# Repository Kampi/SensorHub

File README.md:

# SensorHub

## Table of Contents

- [SensorHub](#sensorhub)
  - [Table of Contents](#table-of-contents)
  - [About](#about)
  - [Image sources](#image-sources)
  - [Setup](#setup)
  - [Device modes](#device-modes)
  - [Bluetooth](#bluetooth)
  - [Measurement](#measurement)
  - [History](#history)
  - [Maintainer](#maintainer)

## About

Solar-powered, low energy environment sensor node with WiFi interface. The device will measure the following parameter:

- Temperature (with a [MCP9808](http://ww1.microchip.com/downloads/en/DeviceDoc/25095A.pdf))
- Humidity (with a [BME680](https://www.bosch-sensortec.com/media/boschsensortec/downloads/datasheets/bst-bme680-ds001.pdf))
- Pressure (with a [BME680](https://www.bosch-sensortec.com/media/boschsensortec/downloads/datasheets/bst-bme680-ds001.pdf))
- Gas resistance (with a [BME680](https://www.bosch-sensortec.com/media/boschsensortec/downloads/datasheets/bst-bme680-ds001.pdf))
- Ambient light (with a [BH1726](https://fscdn.rohm.com/en/products/databook/datasheet/ic/sensor/light/bh1726nuc-e.pdf))
- UV (with a [VEML6070](https://www.vishay.com/docs/84277/veml6070.pdf))

The whole device is designed for low power operation and for a solar panel as current source. A backup battery will be used to buffer the sun-free time during the night or on cloudy days.
This battery will be charged by an integrated solar-charging circuit.

The integrated WiFi is used to transmit the data as an [MQTT](http://mqtt.org/) message to a broker (i. e. a Raspberry Pi). The included Qt application for the Raspberry Pi can be used to visualize and record the received data.

Please visit the [project site](https://www.kampis-elektroecke.de/wetterdaten-aufzeichnen/) or write me an [e-mail](mailto:DanielKampert@kampis-elektroecke.de) when you need additional informations or if you have any questions.

## Image sources

- [Language Icons](https://www.iconfinder.com/iconsets/flags_gosquared)
- [Icons8](https://icons8.com/icon/set/database/material)
- [Qt project](https://www.qt.io/blog/2016/06/20/introducing-new-built-with-qt-logo)

## Setup

- You have to use the [Particle CLI](https://docs.particle.io/reference/developer-tools/cli/) or the [Particle App](https://play.google.com/store/apps/details?id=io.particle.android.app&hl=de) to setup your WiFi credentials in the microcontroller module before you can use the software.

```bash
$ particle usb start-listening
Done.

$ particle serial wifi
? Should I scan for nearby Wi-Fi networks? (Y/n) y
? Should I scan for nearby Wi-Fi networks? Yes
? SSID ...
? SSID ...
? Security Type (Use arrow keys)
? Security Type ...
? Cipher Type (Use arrow keys)
? Cipher Type ...
? Wi-Fi Password ...
? Wi-Fi Password ...
Done! Your device should now restart.
```

- Download a bluetooth app for your smartphone (i. e. [nRF Connect](https://play.google.com/store/apps/details?id=no.nordicsemi.android.mcp&hl=de)).
- Make sure that your microcontroller module runs at least firmware version [1.5.2](https://github.com/particle-iot/device-os/releases/tag/v1.5.2).
- **Optional:** Build the firmware from the soures in `software/SensorHub` by using [Visual Studio Code](https://code.visualstudio.com/) and the [Particle Workbench](https://www.particle.io/workbench/).
- Power up the `SensorHub` and flash the firmware from `software/release` by using the [Particle CLI](https://docs.particle.io/tutorials/developer-tools/cli/#flashing-over-serial-for-the-electron).
- Hold the `MODE` button of the microcontroller module to enter the setup mode.
- After entering the setup mode the RGB LED of the device will lights up red.
- Open the app and connect your smartphone with the `SensorHub`. When the connection is successful the RGB LED of the `SensorHub` starts to blink green until. The device is now ready for configuration until you close the connection.

## Device modes

The `SensorHub` use the RGB led of the microcontroller module to display his current state. Each state is encoded in a blink pattern which begins with a **3 seconds** group color.

| **RGB color** | **Group** |
|:-------------:|:---------:|
| Blue          | Sensors   |
| Green         | Network   |
| Red           | Device    |

The group color is followed by the error code which is encoded with a white flashing of the RGB LED. Each flash has a duration of **1 second**.

| **Blink code** | **Sensors** | **Network** | **Device** |
|:--------------:|:------------------------------------------:|:-----------:|:-----------:|
| 1x             | Temperature sensor failure. | No valid WiFi credentials found. <br> Please use the [Particle CLI](https://docs.particle.io/reference/developer-tools/cli/) to setup your WiFi credentials. | - |
| 2x             | Light sensor failure. | No valid IP address found. | - |
| 3x             | Environment sensor failure. | Connection error. | - |
| 4x             | UV sensor failure. | Network timeout. | - |
| 5x             | Communication error. | - | - |

The current device error is also printed over the serial interface of the microcontroller module or is published over the MQTT tag `sensorhub/errors` (this required valid network settings).

## Bluetooth

The firmware use the following UUIDs for the bluetooth low energy service:

| **UUID** | **Description** |
|:------------------------------------:|:---------:|
| b4250401-fb4b-4746-b2b0-93f0e61122c6 | General service UUID for the BLE service. |
| b4250402-fb4b-4746-b2b0-93f0e61122c6 | MQTT broker IP UUID to configure the IP address of the MQTT broker. |
| b4250403-fb4b-4746-b2b0-93f0e61122c6 | MQTT broker port UUID to configure the port of the MQTT broker. |
| b4250404-fb4b-4746-b2b0-93f0e61122c6 | Sleep time UUID to configure the sleep time of the firmware. |

## Measurement

After a successful configuration and initialization the device will enter the sleep mode. The microcontroller is woken up every three minutes to read in new data from the sensors. After a successful read of the
sensors the data gets packed in a [JSON](https://www.json.org/json-en.html) structure and published by using the [MQTT](http://mqtt.org/) protocol. The firmware uses the topics `sensorhub/weather` to publish the sensor data and the topics `sensorhub/system` and `sensorhub/errors` to publish system messages in the network.
The JSON objects uses the following structure:

`sensorhub/weather`:

```json
{
  "Temperature": "23.0",
  "Ambient light": "1000.0",
  "UV": "7",
  "Pressure": "1004",
  "Humidity": "44.0",
  "Gas resistance": "20000",
  "Gas valid": "0",
  "IAQ": "97.5",
  "IAQ valid": "0",
}
```

`sensorhub/system`:

```json
{
  "Solar": "1.2",
  "Battery": "3.3"
}
```

`sensorhub/errors`:

```txt
This is an error message
```

| **Element**    | **Description** |
|:--------------:|:---------------:|
| Temperature    | Temperature as float in °C. |
| Ambient light  | Illuminance as float in lux. |
| UV             | UV-A index as byte in the range of 0 to 11. |
| Pressure       | Air pressure as float in hPa. |
| Humidity       | Humidity as float in %RH. |
| Gas resistance | Gas resistance as float in Ohms. |
| Gas valid      | Boolean flag to indicate a valid gas measurement. |
| IAQ            | [Indor Air Quality](https://en.wikipedia.org/wiki/Indoor_air_quality) in %. |
| IAQ valid      | Boolean flag to indicate a valid IAQ index. |
| Solar          | Solar cell voltage as float in V. |
| Battery        | Battery voltage as float in V. |

## History

| **Version**   | **Description** | **Date**   |
|-------------|---------------------------------------------|----------|
| 0.1           | Release hardware version 1.1 <br> Firmware version 1.0 <br> Release application version 1.0 | 13.07.2020 |
| 0.2           | Release hardware version 1.2 <br> Improve firmware and release firmware 1.1 <br> Release application version 1.1 | 18.07.2020 |
| 0.3           | Release housing version 1.0 <br> Release firmware 1.2|  |

## Maintainer

- [Daniel Kampert](mailto:DanielKampert@kampis-elektroecke.de)

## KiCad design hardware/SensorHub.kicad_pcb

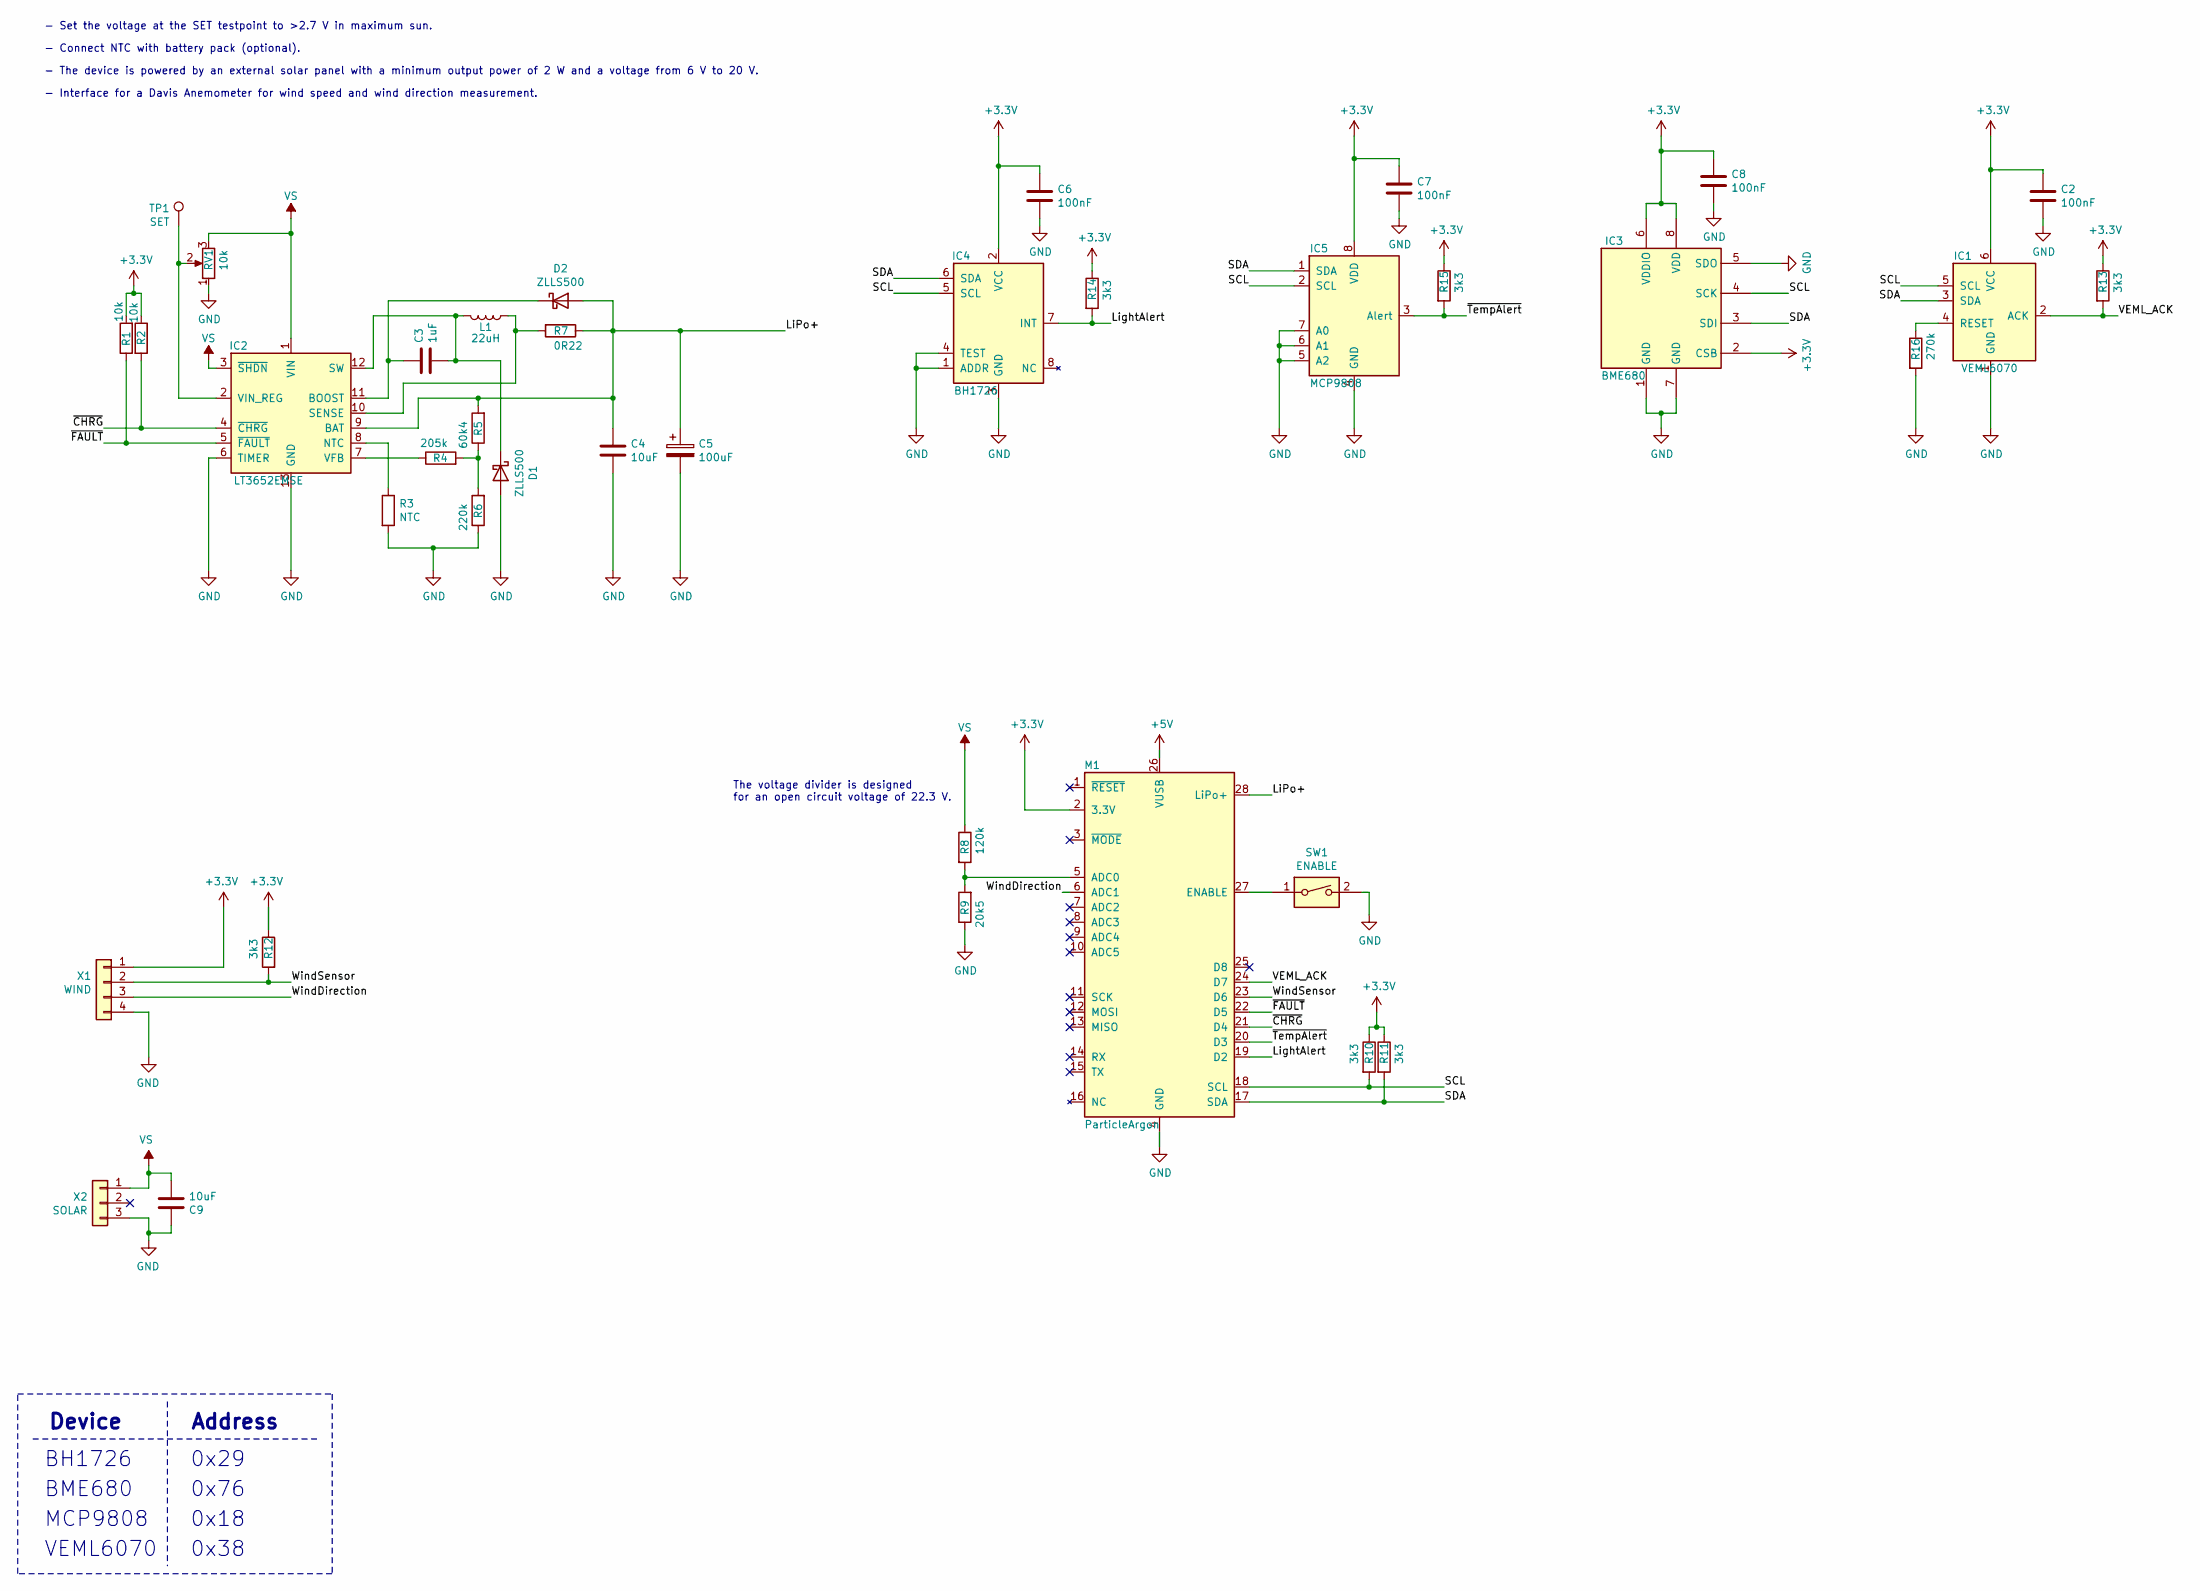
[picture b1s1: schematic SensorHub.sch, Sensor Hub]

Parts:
C2, C6, C7, C8: 100nF; C_0805_2012Metric_Pad1.15x1.40mm_HandSolder
C3: 1uF; C_0805_2012Metric_Pad1.15x1.40mm_HandSolder
C4, C9: 10uF; C_0805_2012Metric_Pad1.15x1.40mm_HandSolder
C5: 100uF; CP_EIA-1608-08_AVX-J_Pad1.25x1.05mm_HandSolder
D1, D2: ZLLS500; D_SOT-23_ANK
IC1: VEML6070; OPLGA-6
IC2: LT3652EMSE; MSOP-12-1EP_3x4mm_P0.65mm_EP1.65x2.85mm
IC3: BME680; Bosch_LGA-8_3x3mm_P0.8mm_ClockwisePinNumbering
IC4: BH1726; WSON-8-1EP_2x2mm_P0.5mm_EP0.9x1.6mm
IC5: MCP9808; MSOP-8_3x3mm_P0.65mm; Mouser 579-MCP9808T-E/MS
L1: 22uH; L_2512_6332Metric_Pad1.52x3.35mm_HandSolder
M1: ParticleArgon; Mfr. Particle
R1, R2: 10k; R_0805_2012Metric_Pad1.15x1.40mm_HandSolder
R3: NTC; PinHeader_1x02_P2.54mm_Vertical
R4: 205k; R_0805_2012Metric_Pad1.15x1.40mm_HandSolder
R5: 60k4; R_0805_2012Metric_Pad1.15x1.40mm_HandSolder
R6: 220k; R_0805_2012Metric_Pad1.15x1.40mm_HandSolder
R7: 0R22; R_0805_2012Metric_Pad1.15x1.40mm_HandSolder
R8: 120k; R_0805_2012Metric_Pad1.15x1.40mm_HandSolder
R9: 20k5; R_0805_2012Metric_Pad1.15x1.40mm_HandSolder
R10, R11, R12, R13, R14, R15: 3k3; R_0805_2012Metric_Pad1.15x1.40mm_HandSolder
R16: 270k; R_0805_2012Metric_Pad1.15x1.40mm_HandSolder
RV1: 10k; Potentiometer_Vishay_TS53YJ_Vertical
SW1: ENABLE; SW_DIP_SPSTx01_Slide_Omron_A6S-110x_W8.9mm_P2.54mm
TP1: SET; TestPoint_Pad_1.5x1.5mm
X1: WIND; 3-2172067-2
X2: SOLAR; 2-2172067-2

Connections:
+3V3: C2.1, C6.1, C7.1, C8.1, IC1.6 (VCC), IC3.2 (CSB), IC3.6 (VDDIO), IC3.8 (VDD), IC4.2 (VCC), IC5.8 (VDD), M1.2 (3.3V), R1.2, R2.1, R10.1, R11.1, R12.1, R13.1, R14.1, R15.1, X1.1
+5V: M1.26 (VUSB)
/LiPo+: C4.1, C5.1, D2.2 (A), IC2.9 (BAT), M1.28 (LiPo+), R5.2, R7.1
/LightAlert: IC4.7 (INT), M1.19 (D2), R14.2
/SCL: IC1.5 (SCL), IC3.4 (SCK), IC4.5 (SCL), IC5.2 (SCL), M1.18 (SCL), R10.2
/SDA: IC1.3 (SDA), IC3.3 (SDI), IC4.6 (SDA), IC5.1 (SDA), M1.17 (SDA), R11.2
/VEML_ACK: IC1.2 (ACK), M1.24 (D7), R13.2
/WindDirection: M1.6 (ADC1), X1.3
/WindSensor: M1.23 (D6), R12.2, X1.2
/~CHRG: IC2.4 (~CHRG), M1.21 (D4), R2.2
/~FAULT: IC2.5 (~FAULT), M1.22 (D5), R1.1
/~TempAlert: IC5.3 (Alert), M1.20 (D3), R15.2
GND: C2.2, C4.2, C5.2, C6.2, C7.2, C8.2, C9.1, D1.2 (A), IC1.1 (GND), IC2.6 (TIMER), IC2.13 (GND), IC3.1 (GND), IC3.5 (SDO), IC3.7 (GND), IC4.1 (ADDR), IC4.3 (GND), IC4.4 (TEST), IC5.4 (GND), IC5.5 (A2), IC5.6 (A1), IC5.7 (A0), M1.4 (GND), R3.2, R6.1, R9.1, R16.2, RV1.1, SW1.2, X1.4, X2.3
unnamed: C3.1, D2.1 (K), IC2.11 (BOOST)
unnamed: C3.2, D1.1 (K), IC2.12 (SW), L1.2
unnamed: IC1.4 (RESET), R16.1
unnamed: IC2.2 (VIN_REG), RV1.2, TP1.1
unnamed: IC2.7 (VFB), R4.1
unnamed: IC2.8 (NTC), R3.1
unnamed: IC2.10 (SENSE), L1.1, R7.2
unnamed: M1.5 (ADC0), R8.2, R9.2
unnamed: M1.27 (ENABLE), SW1.1
unnamed: R4.2, R5.1, R6.2
VS: C9.2, IC2.1 (VIN), IC2.3 (~SHDN), R8.1, RV1.3, X2.1

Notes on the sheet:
- Connect NTC with battery pack (optional).
- Set the voltage at the SET testpoint to >2.7 V in maximum sun.
Device
Address
BH1726
BME680
MCP9808
0x29
0x76
0x18
- The device is powered by an external solar panel with a minimum output power of 2 W and a voltage from 6 V to 20 V.
- Interface for a Davis Anemometer for wind speed and wind direction measurement.
VEML6070
0x38
The voltage divider is designed for an open circuit voltage of 22.3 V.

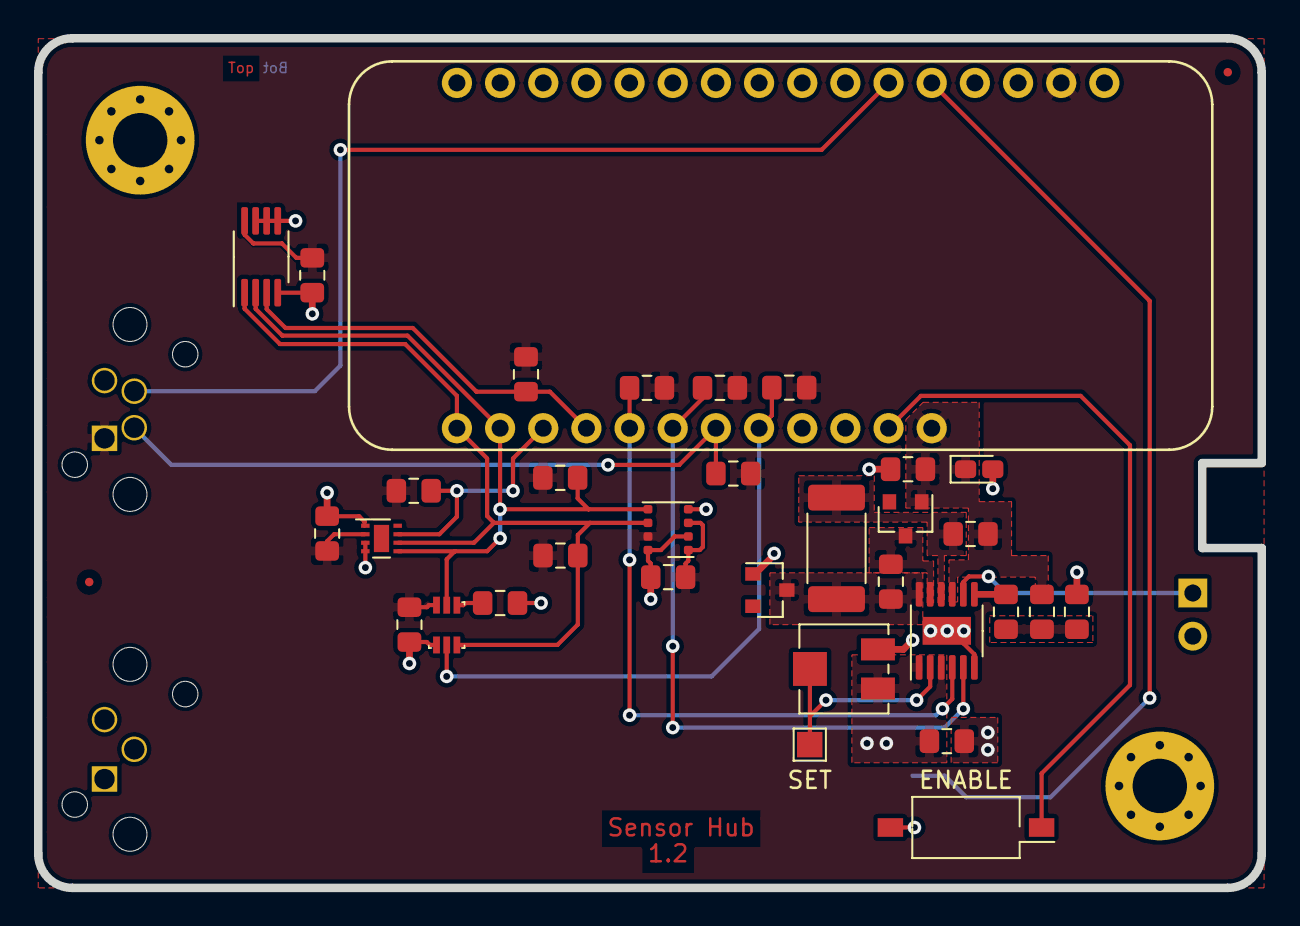
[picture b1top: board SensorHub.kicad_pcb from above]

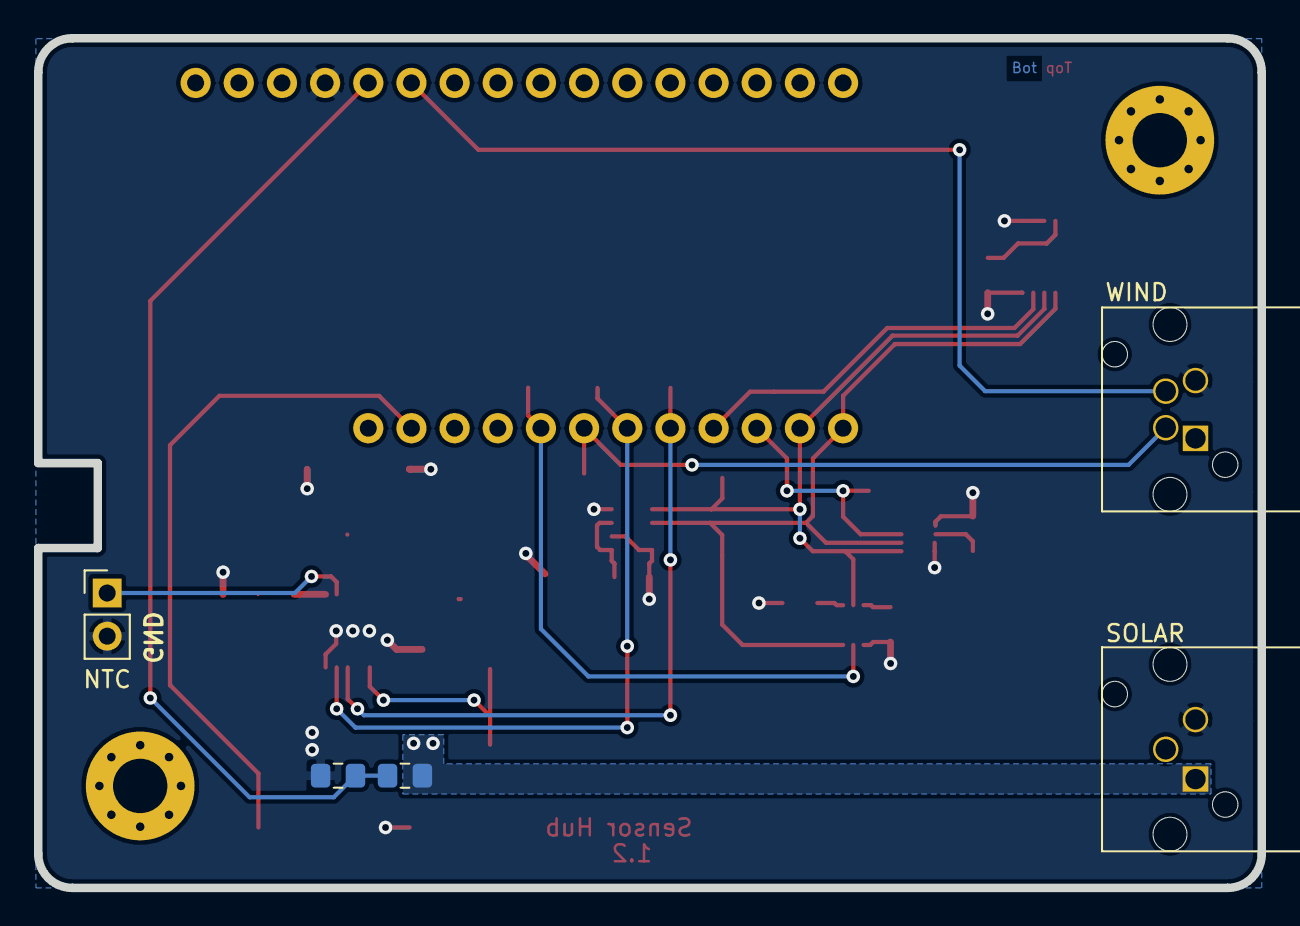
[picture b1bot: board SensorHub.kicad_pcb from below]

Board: 2 copper layers, 72.0 x 50.0 mm, 38 parts (5 on the bottom side), 23 nets.

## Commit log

2020-07-12 Init branch
2020-07-12 Firmware release 1.0
2020-07-13 Recreate for clean up
2020-07-13 Clean up hardware files
2020-07-13 Optimize LTC3652 layout
2020-07-13 Remove pick & place file
2020-07-14 Update README, BOM and schematics
2020-07-14 Add solar voltage measurement to 'Sensors' class and to MQTT message
2020-07-15 Fix wrong footprint for 'power' and 'wind' connector
2020-07-15 - Add battery voltage measurement to MQTT message - Create new firmware release - Update README
2020-07-17 - Firmware version 1.1 test successful
2020-07-18 Release hardware version 1.2
2020-07-18 Release application version 1.1
    - Add new message elements to application
    - Optimize GUI
    - Fix unusable logging function
2020-07-18 - Change the values of the three feedback resistors ('R4', 'R5' and 'R6')
2020-07-18 Change values for 'R8' and 'R9' to support 20 V solar cells
2020-07-18 - Update README - New firmware release - Use 'DATA1' for BH1726 measurement now
2020-07-18 - Change 'R5' to 60.4k Ohms
2020-07-18 Add CHANGELOG
2020-07-18 Clean up files
2020-07-22 - Update README - Add new MQTT topic 'sensorhub/system' for system messages - Move solar and battery voltage to 'sensorhub/system' - Add null pointer check for MQTT callback - Add bluetooth character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
2020-07-22 Remove VS code settings
2020-07-25 Working on housing - Remove screw nut for pressure compensation element - Add thread for presure compensation element - Change spacer - Change screws - Change the housing in the BOM to the light gray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
    Misc:
    - Print new BOM PDF
    - Add drawing for the housing
2020-07-27 Update drawings for the housing
2020-08-10 Housing: - Change the diameter of the connector drilling holes to 8.6 mm
2020-08-10 Housing: - Change the diameter of the connector drillings to 8.5 mm
2020-08-16 Misc: - Update README
    Network:
    - Add BLE characteristic for MQTT broker port
    SensorHub:
    - Reorder console message
